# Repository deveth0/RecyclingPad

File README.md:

# Recycling Pad

This repository contains all required files to build a `Recycling Pad` which is a plugin extension for the [Keygem Switch Tester](https://keygem.store/collections/switch-testers/products/switch-tester-3x3).

It features 3x3 keys, whereby any of the upper three once can be replaced by EC11 encoder(s).

## Gallery

[Fancy Images by @Xibaris](https://imgur.com/a/etkFRNU)

## Required Parts

* 1x PCB
* 1x Pro Micro Controller
* 9x 1n4148 Diode (thru hole)
* 1x 6mm tactile switch (to reset MCU)
* up to 3 EC11 Encoders
* up to 9 Cherry-style mechanical switches
* up to 18 Millmax Sockets 3305 / 7305 (recommended, for hotswap)
* 4x 3.5mm Spacer (3d Print file available) => [Spacer 3.5mm](./Case/Recycling_Pad-Spacer_3,5mm.stl)
* 4x 6mm Spacer (3d Print file available) => [Spacer 6mm](./Case/Recycling_Pad-Spacer_9mm.stl)

Depending on your setup, you can replace any number of the upper switches with EC11 rotary encoders.

## Assembly

As the whole PCB is quite tight packed, you need to keep an eye on the soldering order. If you use Millmax Sockets, it's getting easier as you can remove the switches if required.

1. First solder in all the diodes and the reset switch
2. Then add the MillMax Sockets
3. Solder in the center EC11 encoder (if used)
3. Solder in the Pro Micro Headers (NOT THE Controler)
4. Solder in the the remaining EC11 Encoder (use plate as guide to keep the encoder aligned)
5. If not using Millmax: Add all switches to the plate and solder in the switches
5. Add the controller to the Headers

Depending on the length of your Headers, you might want to cut them after soldering. Otherwise they might touch the PCB and shortcircuit a switch.

## QMK

The `qmk` folder contains some base configurations for the Pad.

Note: rows and columns are switched, therefor your configuration needs to be rotated 90° (see example configs).

## Acknowledgements

Cherry Switch 3d Model: https://3dwarehouse.sketchup.com/model/81cf92a3e03098a5cc90be332989df6e/Key-switch-Cherry

Kicad Schematics / Footprints: https://github.com/imchipwood/dumbpad/tree/master/combo_oled

Schematics for embedded version: https://github.com/kb-elmo/QEZ

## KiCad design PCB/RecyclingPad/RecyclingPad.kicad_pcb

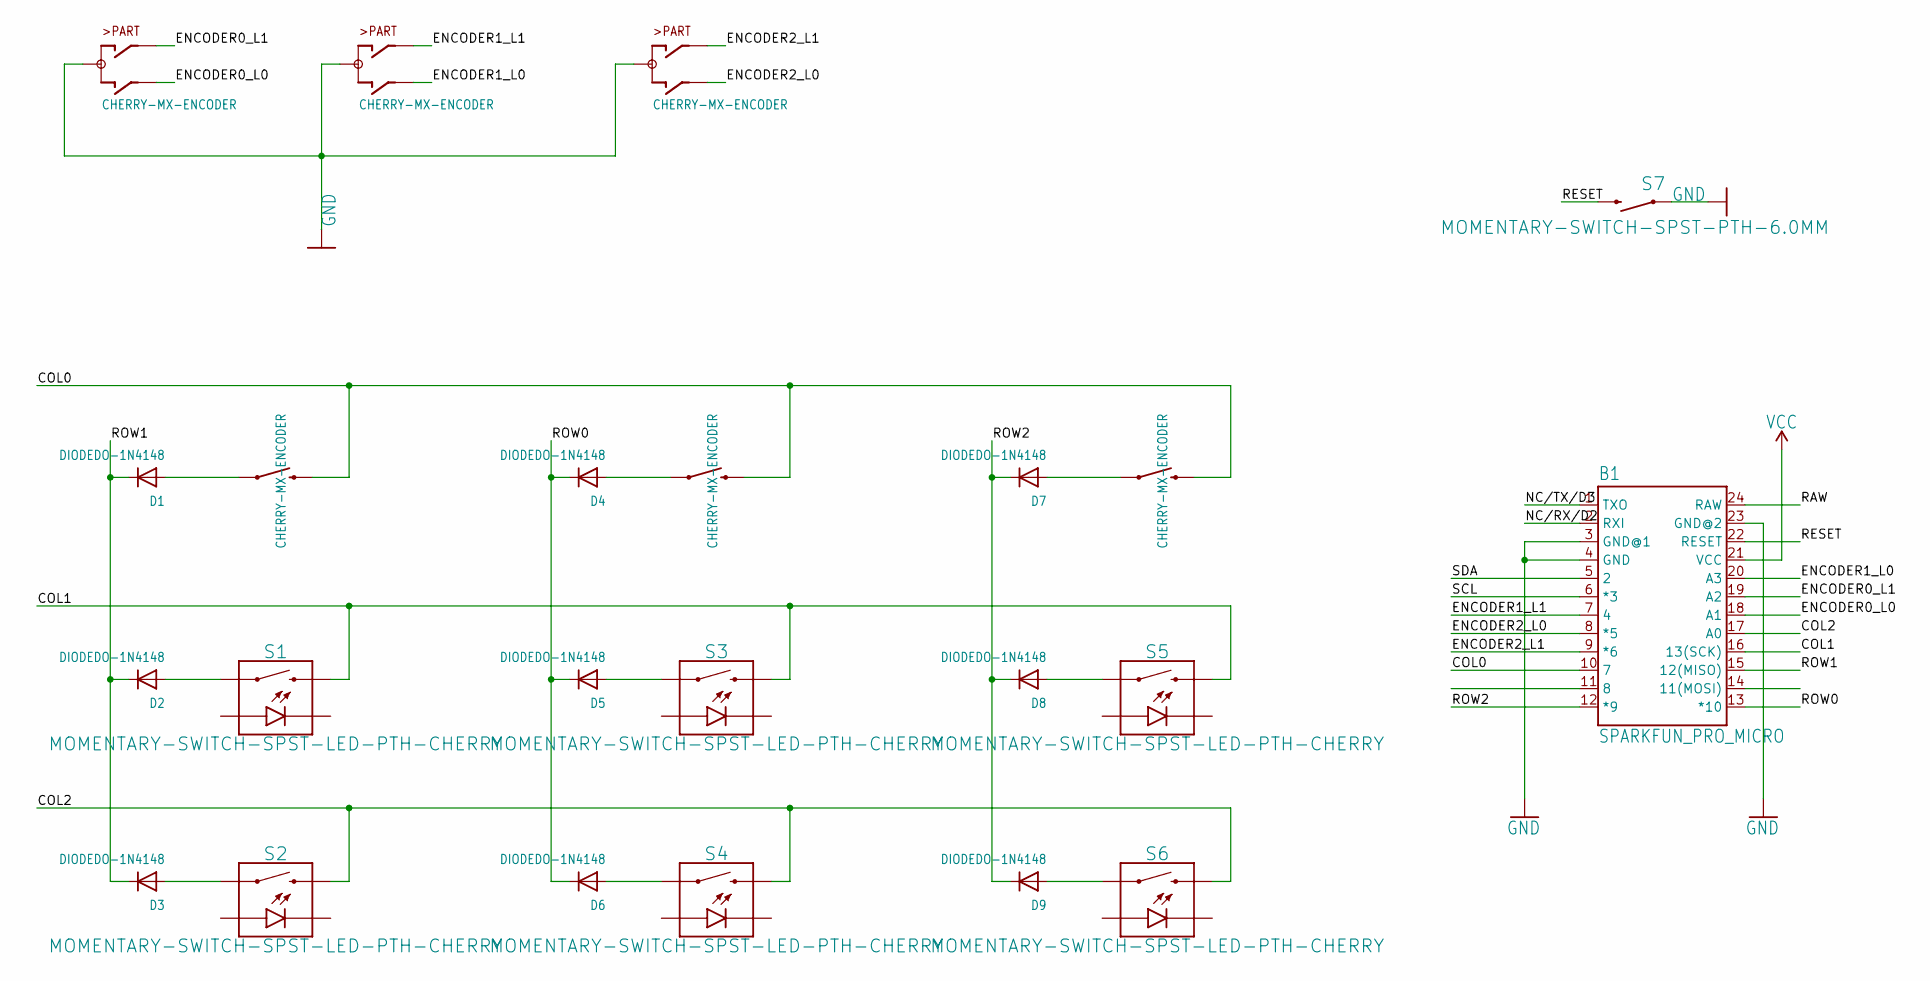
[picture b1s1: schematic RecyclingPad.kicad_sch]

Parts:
B1: SPARKFUN_PRO_MICRO
D1, D2, D3, D4, D5, D6, D7, D8, D9: DIODEDO-1N4148; DO-1N4148
RE_0_1, RE_3_1, RE_3_2: CHERRY-MX-ENCODER
S1, S2, S3, S4, S5, S6: MOMENTARY-SWITCH-SPST-LED-PTH-CHERRY; CHERRY-MX
S7: MOMENTARY-SWITCH-SPST-PTH-6.0MM; TACTILE_SWITCH_PTH_6.0MM

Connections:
/COL0: B1.10 (7), RE_0_1.E (2), RE_0_1.S2 (2), RE_3_1.E (2), RE_3_1.S2 (2), RE_3_2.E (2), RE_3_2.S2 (2)
/COL1: B1.16 (13(SCK)), S1.S2 (2), S3.S2 (2), S5.S2 (2)
/COL2: B1.17 (A0), S2.S2 (2), S4.S2 (2), S6.S2 (2)
/ENCODER0_L0: B1.18 (A1), RE_3_1.B
/ENCODER0_L1: B1.19 (A2), RE_3_1.A
/ENCODER1_L0: B1.20 (A3), RE_0_1.B
/ENCODER1_L1: B1.7 (4), RE_0_1.A
/ENCODER2_L0: B1.8 (*5), RE_3_2.B
/ENCODER2_L1: B1.9 (*6), RE_3_2.A
/NC/RX/D2: B1.2 (RXI)
/NC/TX/D3: B1.1 (TXO)
/RAW: B1.24 (RAW)
/RESET: B1.22 (RESET), S7.3 (2)
/ROW0: B1.13 (*10), D4.C, D5.C, D6.C
/ROW1: B1.15 (12(MISO)), D1.C, D2.C, D3.C
/ROW2: B1.12 (*9), D7.C, D8.C, D9.C
/SCL: B1.6 (*3)
/SDA: B1.5 (2)
GND: B1.3 (GND@1), B1.4 (GND), B1.23 (GND@2), RE_0_1.C, RE_3_1.C, RE_3_2.C, S7.1
unnamed: D1.A, RE_0_1.D (1), RE_0_1.S1 (1)
unnamed: D2.A, S1.S1 (1)
unnamed: D3.A, S2.S1 (1)
unnamed: D4.A, RE_3_1.D (1), RE_3_1.S1 (1)
unnamed: D5.A, S3.S1 (1)
unnamed: D6.A, S4.S1 (1)
unnamed: D7.A, RE_3_2.D (1), RE_3_2.S1 (1)
unnamed: D8.A, S5.S1 (1)
unnamed: D9.A, S6.S1 (1)
VCC: B1.21 (VCC)

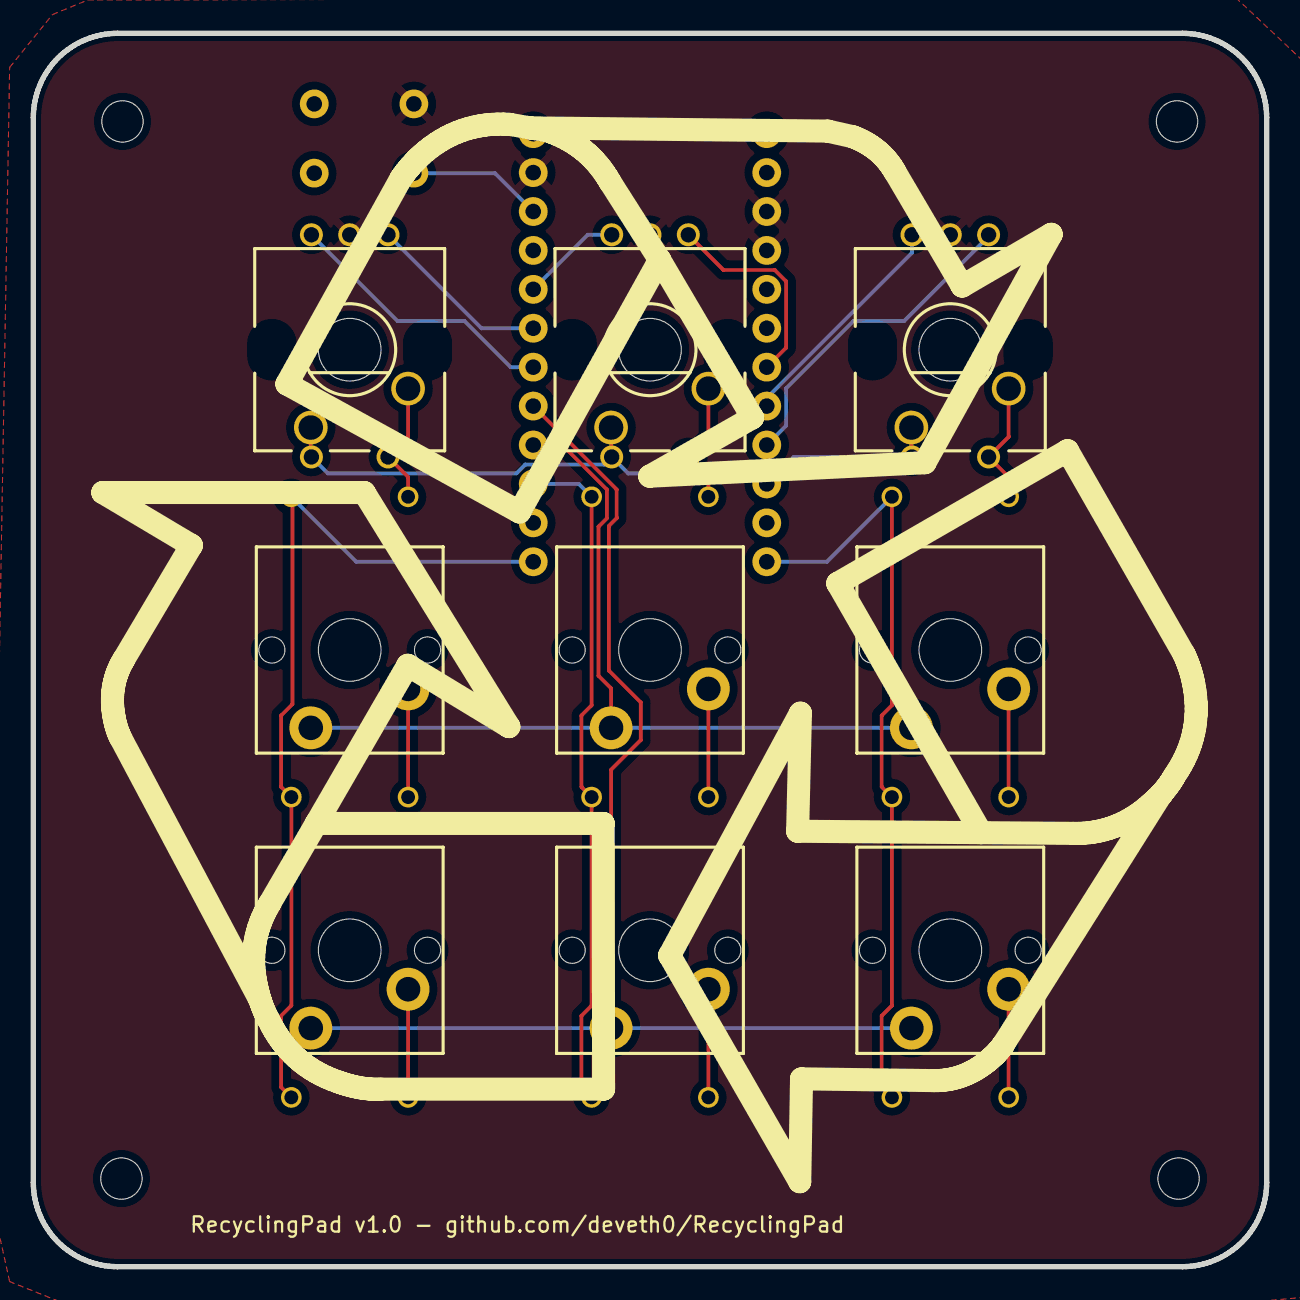
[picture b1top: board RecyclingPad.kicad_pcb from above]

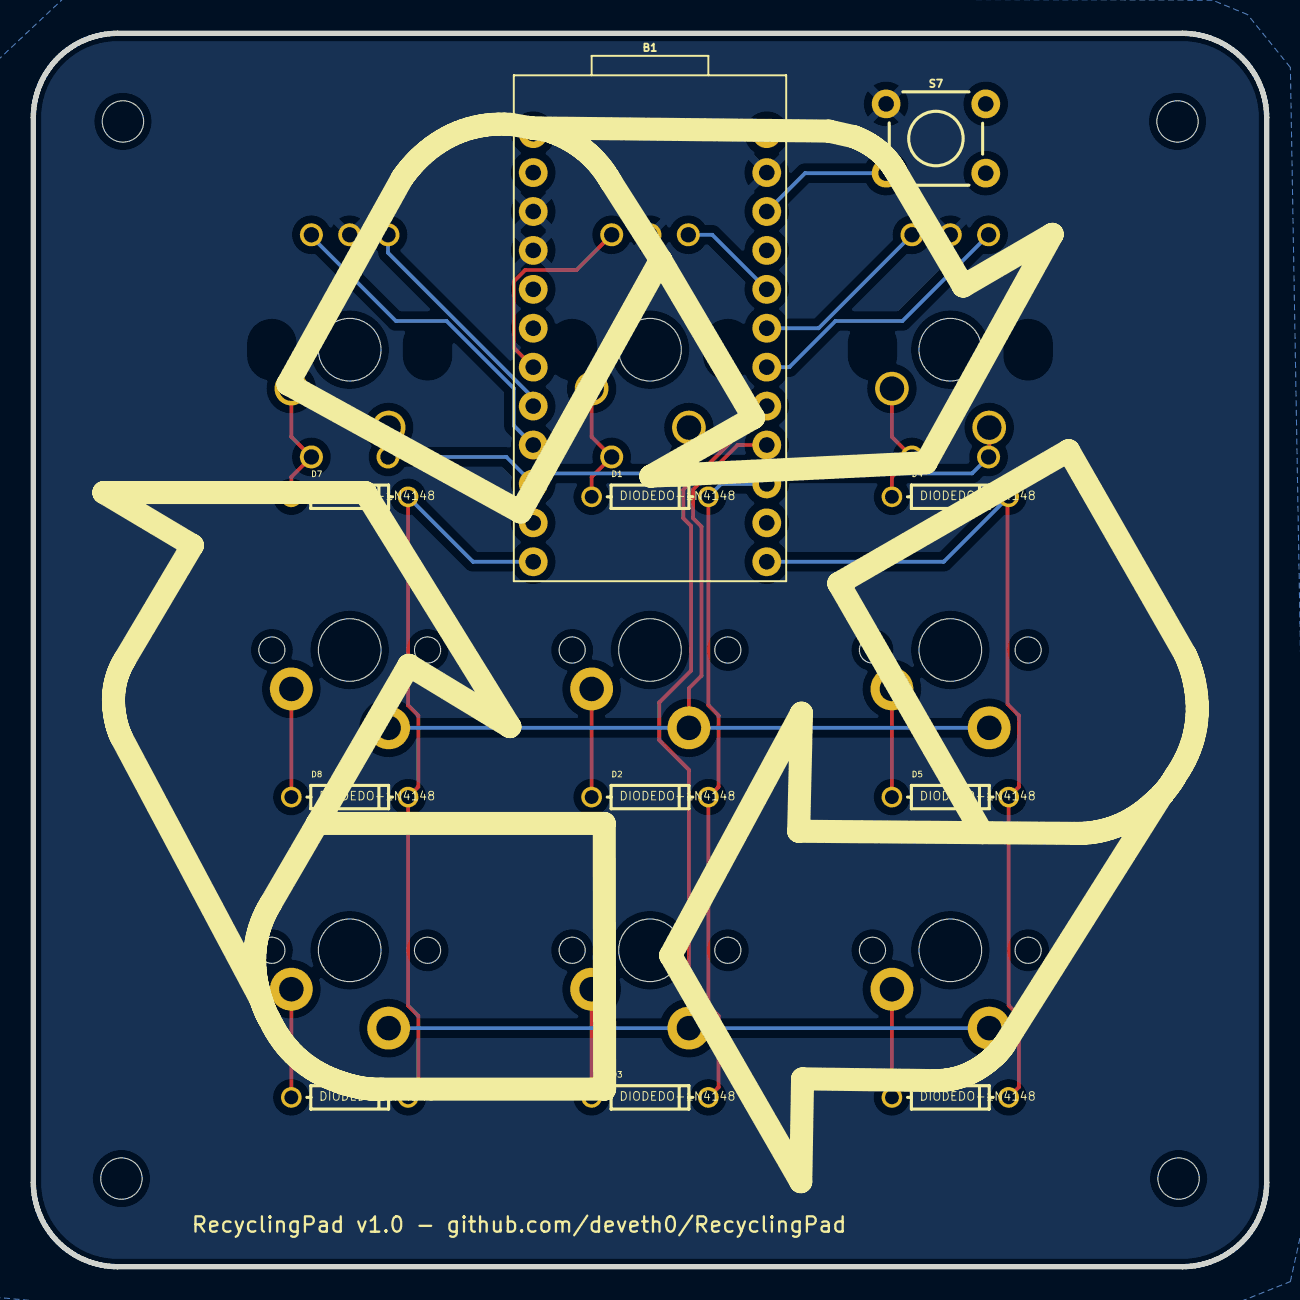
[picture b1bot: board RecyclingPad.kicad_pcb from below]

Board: 2 copper layers, 80.5 x 80.5 mm, 20 parts (11 on the bottom side), 23 nets.

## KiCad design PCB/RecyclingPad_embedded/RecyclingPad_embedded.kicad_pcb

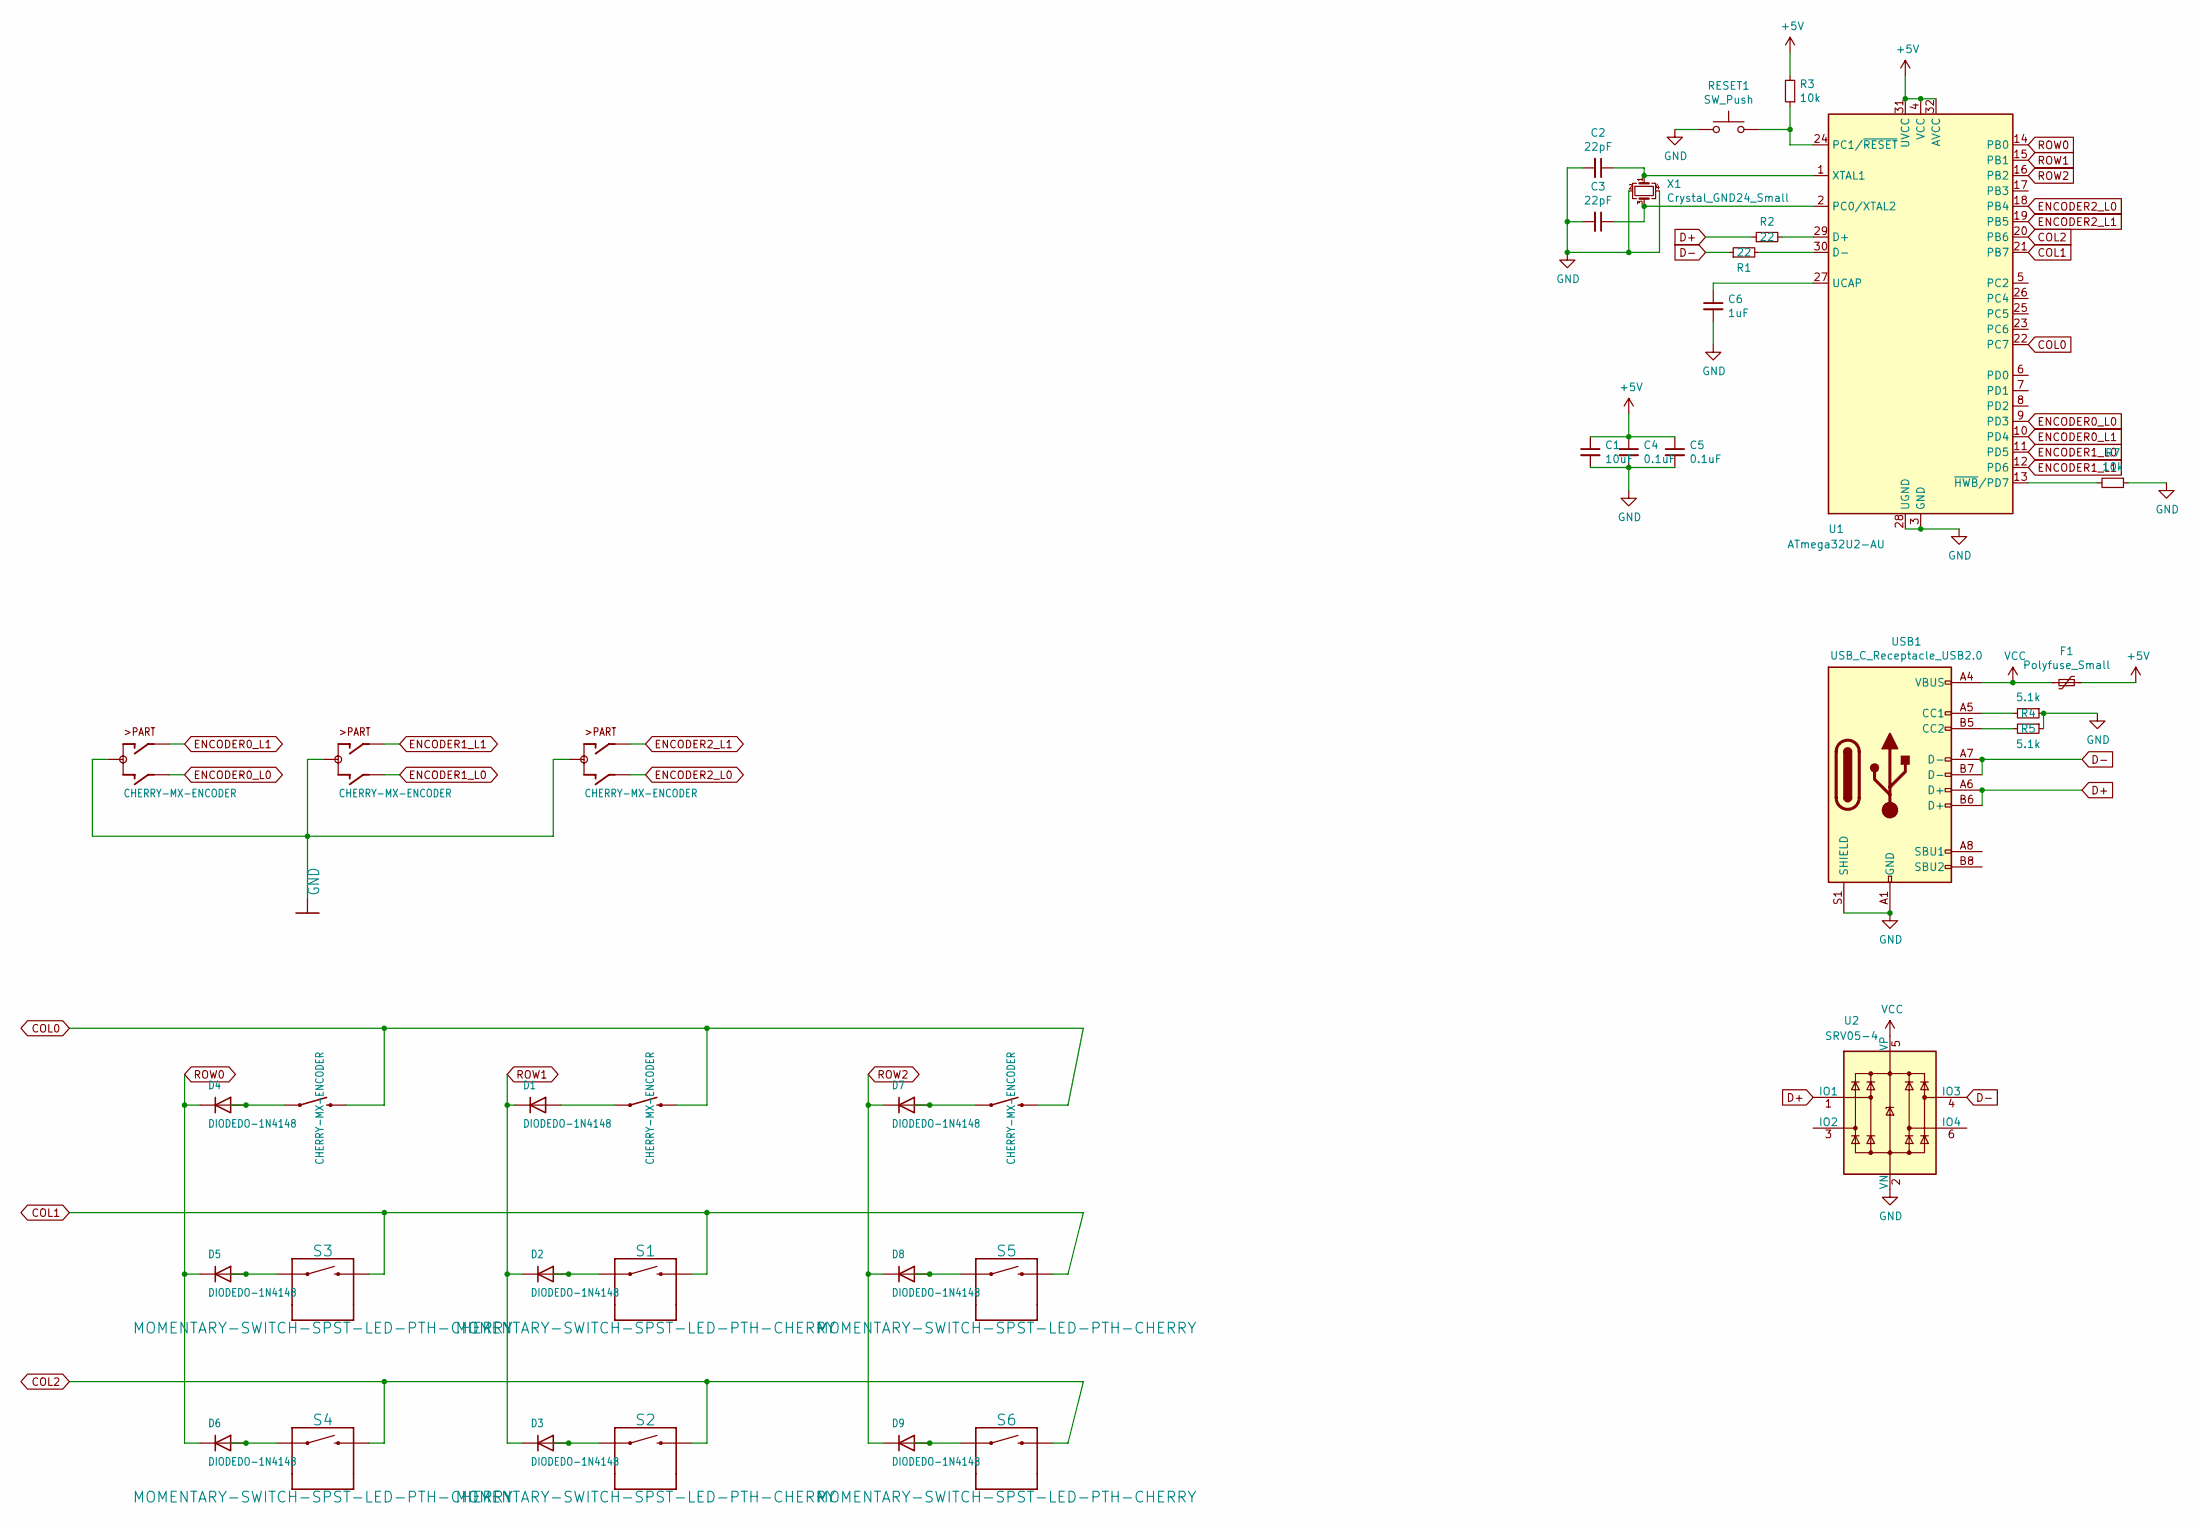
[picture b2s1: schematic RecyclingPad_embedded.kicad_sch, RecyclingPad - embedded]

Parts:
C1: 10uF; C_0805_2012Metric; LCSC Part C91245
C2, C3: 22pF; C_0805_2012Metric; LCSC Part C1804
C4, C5: 0.1uF; C_0805_2012Metric; LCSC Part C49678
C6: 1uF; C_0805_2012Metric; LCSC Part C28323
D1, D2, D3, D4, D5, D6, D7, D8, D9: DIODEDO-1N4148; D_SOD-323; LCSC Part C2128
F1: Polyfuse_Small; Fuse_1206_3216Metric; LCSC Part C69688
R1, R2: 22; R_0805_2012Metric; LCSC Part C17561
R3, R7: 10k; R_0805_2012Metric; LCSC Part C17414
R4, R5: 5.1k; R_0805_2012Metric; LCSC Part C27834
RESET1: SW_Push; SW_SPST_TL3342; LCSC Part C318884
RE_0_1, RE_3_1, RE_3_2: CHERRY-MX-ENCODER
S1, S2, S3, S4, S5, S6: MOMENTARY-SWITCH-SPST-LED-PTH-CHERRY; CHERRY-MX
U1: ATmega32U2-AU; TQFP-32_7x7mm_P0.8mm; LCSC Part C618733
U2: SRV05-4; SOT-23-6; LCSC Part C85364
USB1: USB_C_Receptacle_USB2.0; USB_C_Receptacle_HRO_TYPE-C-31-M-12; LCSC Part C165948
X1: Crystal_GND24_Small; Crystal_SMD_3225-4Pin_3.2x2.5mm; LCSC Part C13738

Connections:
+5V: C1.1, C4.1, C5.1, F1.1, R3.2, U1.4 (VCC), U1.31 (UVCC), U1.32 (AVCC)
COL0: RE_0_1.E (2), RE_0_1.S2 (2), RE_3_1.E (2), RE_3_1.S2 (2), RE_3_2.E (2), RE_3_2.S2 (2), U1.22 (PC7)
COL1: S1.S2 (2), S3.S2 (2), S5.S2 (2), U1.21 (PB7)
COL2: S2.S2 (2), S4.S2 (2), S6.S2 (2), U1.20 (PB6)
D+: R2.1, U2.1 (IO1), USB1.A6 (D+), USB1.B6 (D+)
D-: R1.1, U2.4 (IO3), USB1.A7 (D-), USB1.B7 (D-)
ENCODER0_L0: RE_3_1.B, U1.9 (PD3)
ENCODER0_L1: RE_3_1.A, U1.10 (PD4)
ENCODER1_L0: RE_0_1.B, U1.11 (PD5)
ENCODER1_L1: RE_0_1.A, U1.12 (PD6)
ENCODER2_L0: RE_3_2.B, U1.18 (PB4)
ENCODER2_L1: RE_3_2.A, U1.19 (PB5)
GND: C1.2, C2.2, C3.2, C4.2, C5.2, C6.2, R4.1, R5.1, R7.1, RESET1.1, RE_0_1.C, RE_3_1.C, RE_3_2.C, U1.3 (GND), U1.28 (UGND), U2.2 (VN), USB1.A1 (GND), USB1.A12 (GND), USB1.B1 (GND), USB1.B12 (GND), USB1.S1 (SHIELD), X1.2, X1.4
unnamed: C2.1, U1.1 (XTAL1), X1.1
unnamed: C3.1, U1.2 (PC0/XTAL2), X1.3
unnamed: C6.1, U1.27 (UCAP)
unnamed: D1.2 (A), RE_0_1.D (1), RE_0_1.S1 (1)
unnamed: D2.2 (A), S1.S1 (1)
unnamed: D3.2 (A), S2.S1 (1)
unnamed: D4.2 (A), RE_3_1.D (1), RE_3_1.S1 (1)
unnamed: D5.2 (A), S3.S1 (1)
unnamed: D6.2 (A), S4.S1 (1)
unnamed: D7.2 (A), RE_3_2.D (1), RE_3_2.S1 (1)
unnamed: D8.2 (A), S5.S1 (1)
unnamed: D9.2 (A), S6.S1 (1)
unnamed: R1.2, U1.30 (D-)
unnamed: R2.2, U1.29 (D+)
unnamed: R3.1, RESET1.2, U1.24 (PC1/~RESET)
unnamed: R4.2, USB1.A5 (CC1)
unnamed: R5.2, USB1.B5 (CC2)
unnamed: R7.2, U1.13 (~HWB/PD7)
ROW0: D4.1 (K), D5.1 (K), D6.1 (K), U1.14 (PB0)
ROW1: D1.1 (K), D2.1 (K), D3.1 (K), U1.15 (PB1)
ROW2: D7.1 (K), D8.1 (K), D9.1 (K), U1.16 (PB2)
VCC: F1.2, U2.5 (VP), USB1.A4 (VBUS), USB1.A9 (VBUS), USB1.B4 (VBUS), USB1.B9 (VBUS)

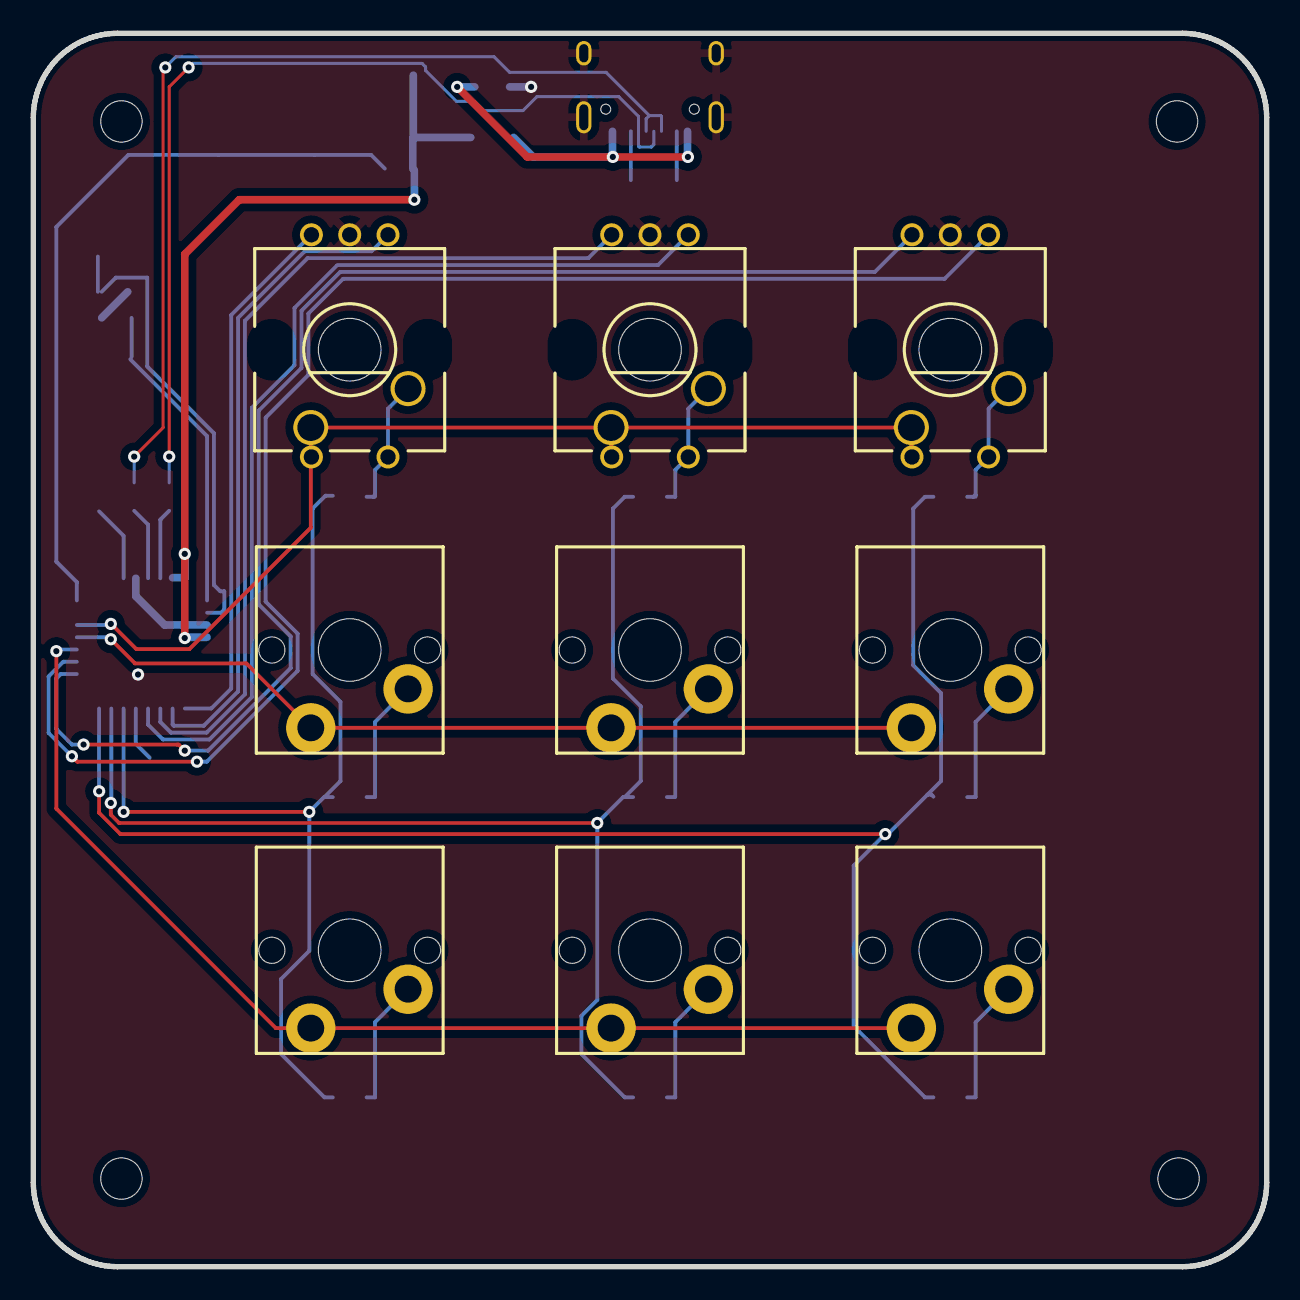
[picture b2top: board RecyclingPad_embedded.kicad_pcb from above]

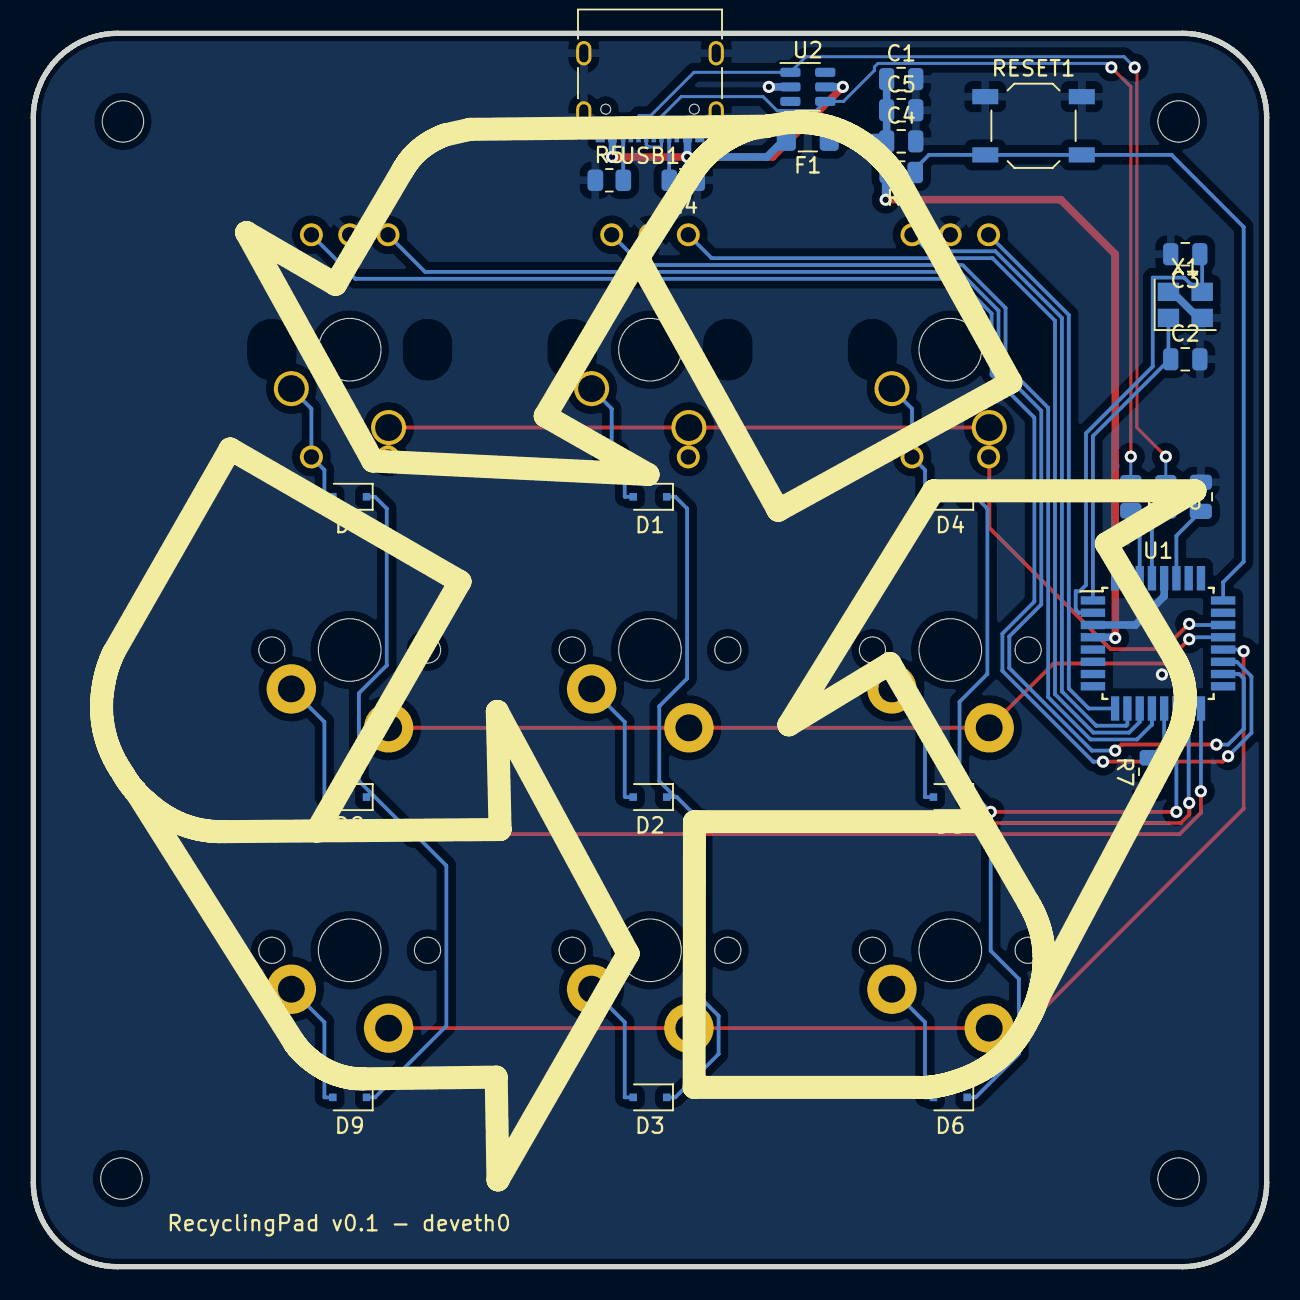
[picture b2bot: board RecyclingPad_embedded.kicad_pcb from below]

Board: 2 copper layers, 80.5 x 80.5 mm, 36 parts (27 on the bottom side), 35 nets.

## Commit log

2022-06-26 FreeCad
2022-06-26 gitignore
2022-06-26 Initial PCB
2022-06-26 Embedded
2022-06-26 Embedded Version
2022-07-01 Update gitignore
2022-07-01 Embedded version of the RecyclingPad
2022-07-01 Embedded Version of the Recycling Pad (untested)
2022-07-01 Basic qmk configs for RecyclingPad v1x
2022-07-05 Add triple encoder
2022-07-05 Initial QMK configs
2022-07-06 Add case printable
2022-07-31 Unique Product ID
2022-12-29 Move USB Config to json
2023-02-20 Update qmk configs
2023-02-21 Add updated via configs
2023-02-22 Change vendorId
